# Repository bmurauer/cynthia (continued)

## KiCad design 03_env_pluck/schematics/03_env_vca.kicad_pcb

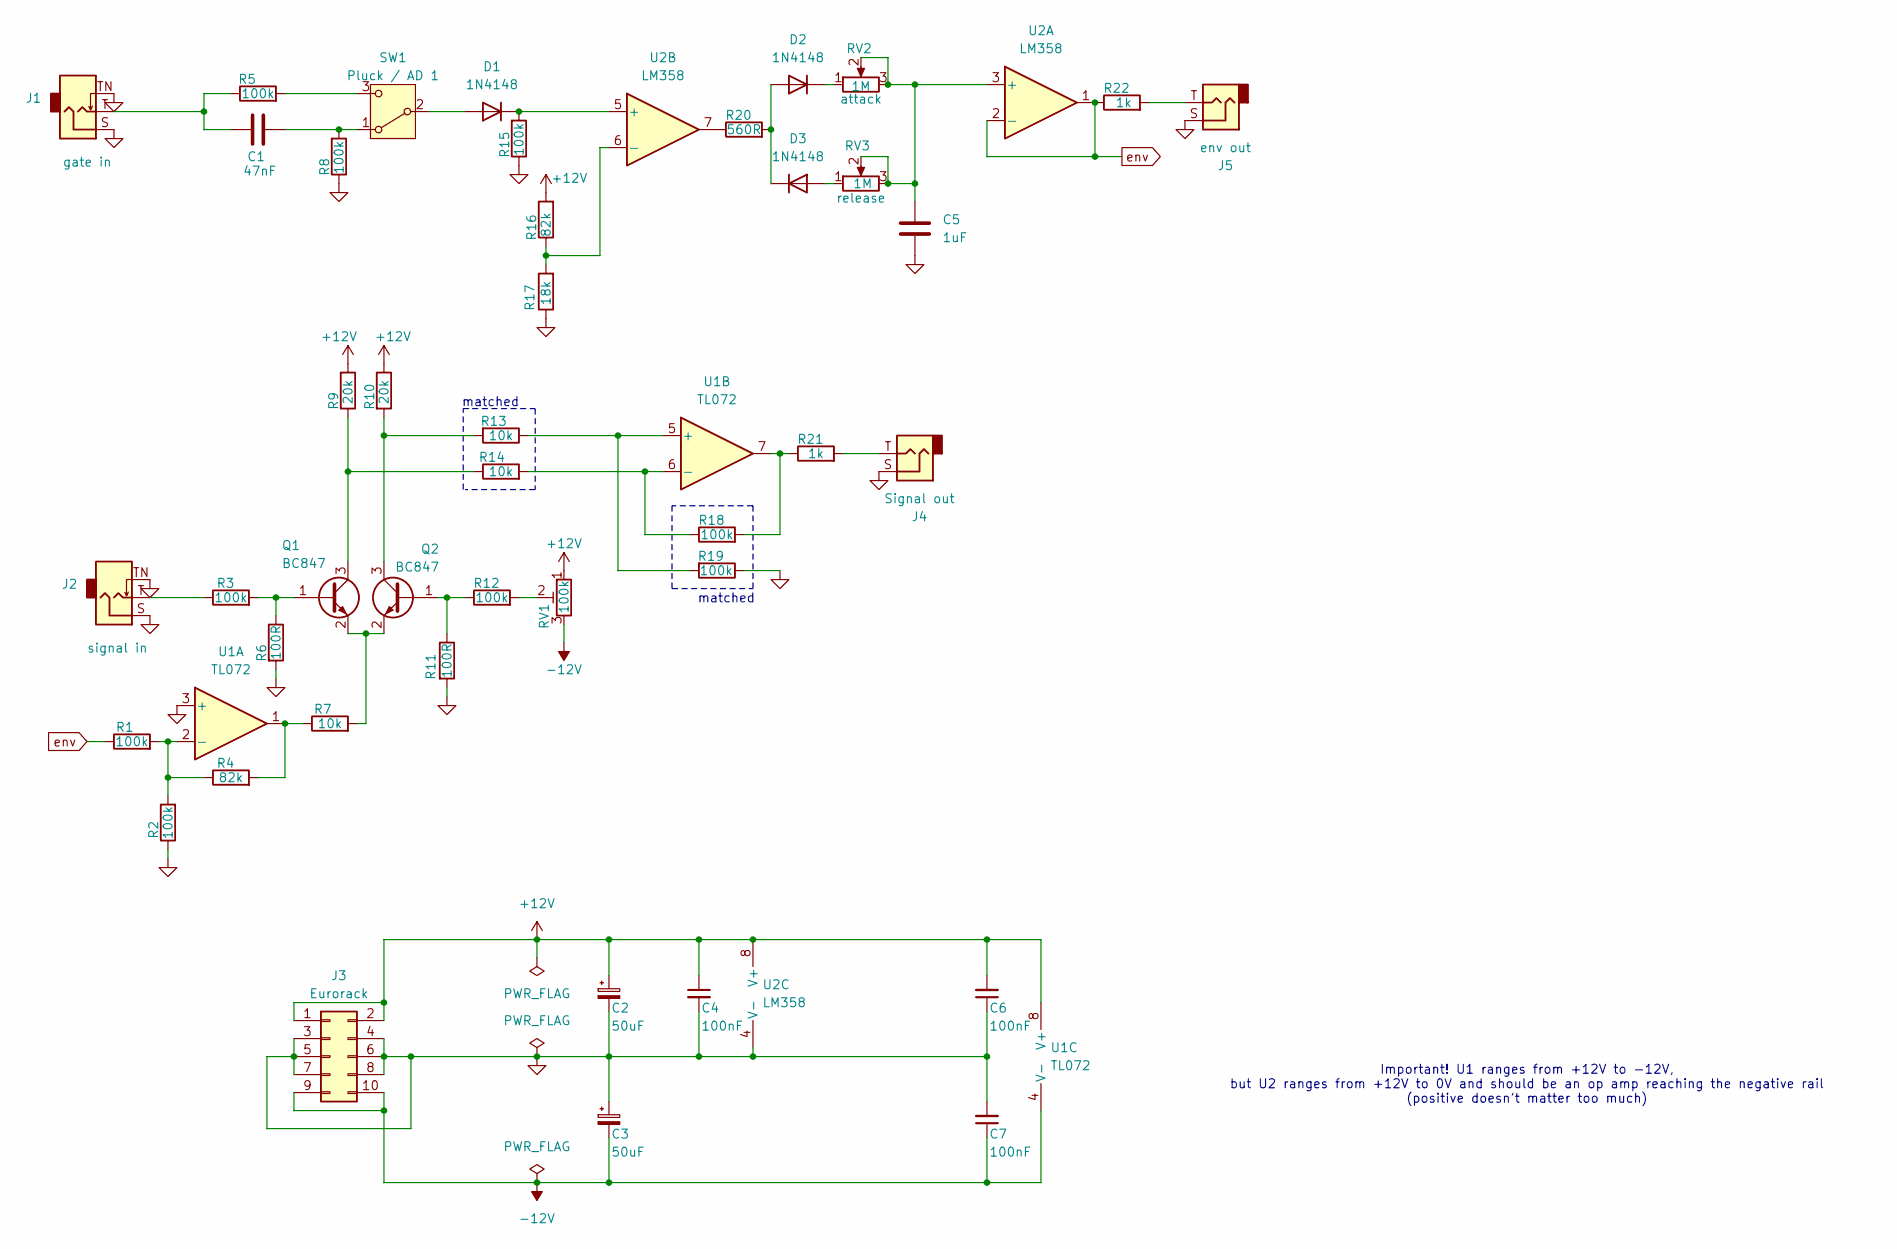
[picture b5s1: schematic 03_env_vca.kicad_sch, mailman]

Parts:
C1: 47nF; C_0805_2012Metric_Pad1.18x1.45mm_HandSolder
C2, C3: 50uF; CP_Radial_D6.3mm_P2.50mm
C4, C6, C7: 100nF; C_0805_2012Metric_Pad1.18x1.45mm_HandSolder
C5: 1uF; C_0805_2012Metric_Pad1.18x1.45mm_HandSolder
D1, D2, D3: 1N4148; D_0805_2012Metric_Pad1.15x1.40mm_HandSolder
J1: gate in; 3.5mm jack mono switched
J2: signal in; 3.5mm jack mono switched
J3: Eurorack; PinHeader_2x05_P2.54mm_Vertical
J4: Signal out; 3.5mm jack mono
J5: env out; 3.5mm jack mono
Q1, Q2: BC847; SOT-23
R1, R2, R3, R5, R8, R12, R15, R18, R19: 100k; R_0805_2012Metric_Pad1.20x1.40mm_HandSolder
R4, R16: 82k; R_0805_2012Metric_Pad1.20x1.40mm_HandSolder
R6, R11: 100R; R_0805_2012Metric_Pad1.20x1.40mm_HandSolder
R7, R13, R14: 10k; R_0805_2012Metric_Pad1.20x1.40mm_HandSolder
R9, R10: 20k; R_0805_2012Metric_Pad1.20x1.40mm_HandSolder
R17: 18k; R_0805_2012Metric_Pad1.20x1.40mm_HandSolder
R20: 560R; R_0805_2012Metric_Pad1.20x1.40mm_HandSolder
R21, R22: 1k; R_0805_2012Metric_Pad1.20x1.40mm_HandSolder
RV1: 100k; trimmer
RV2, RV3: 1M; potientiometer
SW1: Pluck / AD 1; switch
U1: TL072; SOIC-8_3.9x4.9mm_P1.27mm
U2: LM358; SOIC-8_3.9x4.9mm_P1.27mm

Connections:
+12V: C2.1, C4.1, C6.2, J3.1, J3.2, R9.2, R10.1, R16.2, RV1.1, U1.8 (V+), U2.8 (V+)
-12V: C3.2, C7.1, J3.9, J3.10, RV1.3, U1.4 (V-)
GND: C2.2, C3.1, C4.2, C5.2, C6.1, C7.2, J1.S, J1.TN, J2.S, J2.TN, J3.3, J3.4, J3.5, J3.6, J3.7, J3.8, J4.S, J5.S, R2.1, R6.2, R8.1, R11.2, R15.1, R17.1, R19.1, U1.3 (+), U2.4 (V-)
unnamed: C1.1, J1.T, R5.1
unnamed: D1.2 (A), SW1.2 (B)
unnamed: D1.1 (K), R15.2, U2.5 (+)
unnamed: D2.2 (A), D3.1 (K), R20.2
unnamed: D2.1 (K), RV2.1
unnamed: D3.2 (A), RV3.1
unnamed: J2.T, R3.1
unnamed: J4.T, R21.2
unnamed: J5.T, R22.2
unnamed: Q1.1 (B), R3.2, R6.1
unnamed: Q1.3 (C), R9.1, R14.1
unnamed: Q1.2 (E), Q2.2 (E), R7.2
unnamed: Q2.1 (B), R11.1, R12.1
unnamed: Q2.3 (C), R10.2, R13.2
unnamed: R4.2, R7.1, U1.1
unnamed: R12.2, RV1.2
unnamed: R18.2, R21.1, U1.7
unnamed: R20.1, U2.7
unnamed: C1.2, R8.2, SW1.1 (A)
unnamed: R5.2, SW1.3 (C)
unnamed: R1.2, R2.2, R4.1, U1.2 (-)
unnamed: R13.1, R19.2, U1.5 (+)
unnamed: R14.2, R18.1, U1.6 (-)
unnamed: C5.1, RV2.2, RV2.3, RV3.2, RV3.3, U2.3 (+)
unnamed: R16.1, R17.2, U2.6 (-)
env: R1.1, R22.1, U2.1, U2.2 (-)

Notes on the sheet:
matched
Important! U1 ranges from +12V to -12V, but U2 ranges from +12V to 0V and should be an op amp reaching the negative rail (positive doesn't matter too much)

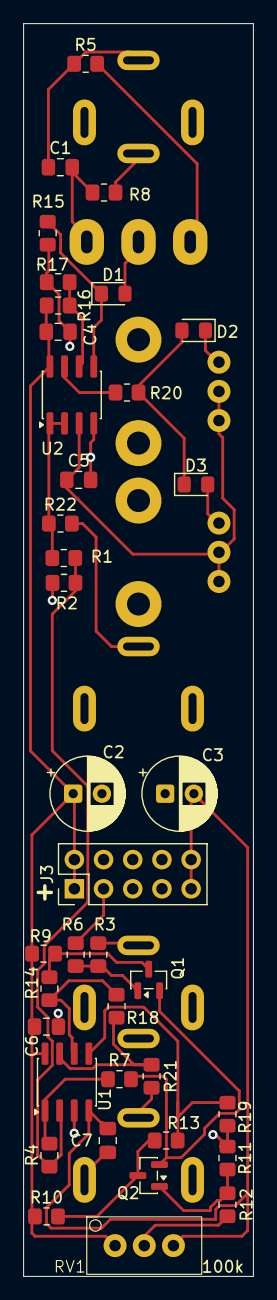
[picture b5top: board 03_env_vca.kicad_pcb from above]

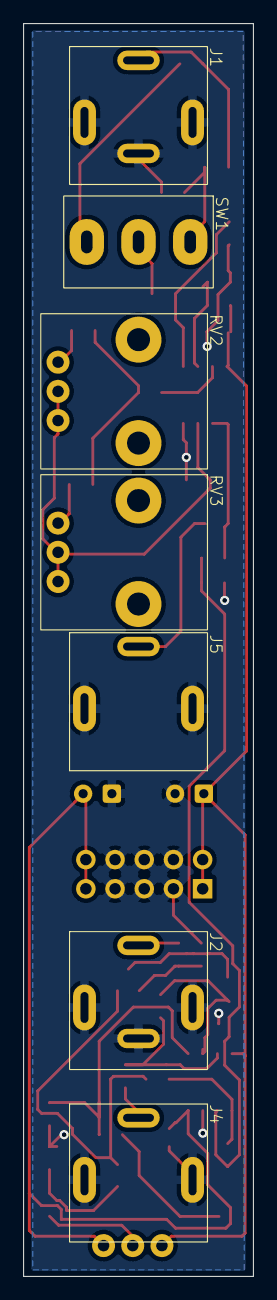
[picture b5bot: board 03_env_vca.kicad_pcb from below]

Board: 2 copper layers, 20.0 x 109.0 mm, 45 parts (7 on the bottom side), 29 nets.

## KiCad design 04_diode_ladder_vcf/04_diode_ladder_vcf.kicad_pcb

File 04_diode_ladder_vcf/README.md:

#04: Diode Ladder VCF

## I/O Specification

Fill in the "Design" columns before building; fill in the "As-Built" columns after assembly and bench testing.

No `.net` file exists for this module yet, so the input/output rows below aren't populated from the schematic. Generate the netlist in KiCad (File > Fabrication Outputs > Netlist, or the equivalent export) and I can fill in the `Ref` / `Label` columns from it — or list the jacks here yourself.

### Inputs

| Ref | Label | Signal Type (Design) | Expected Behavior / Range (Design) | Measured Behavior / Range (As-Built) | Notes |
|-----|-------|-----------------------|--------------------------------------|-----------------------------------------|-------|
| | | | | | |

### Outputs

| Ref | Label | Signal Type (Design) | Expected Behavior / Range (Design) | Measured Behavior / Range (As-Built) | Notes |
|-----|-------|-----------------------|--------------------------------------|-----------------------------------------|-------|
| | | | | | |

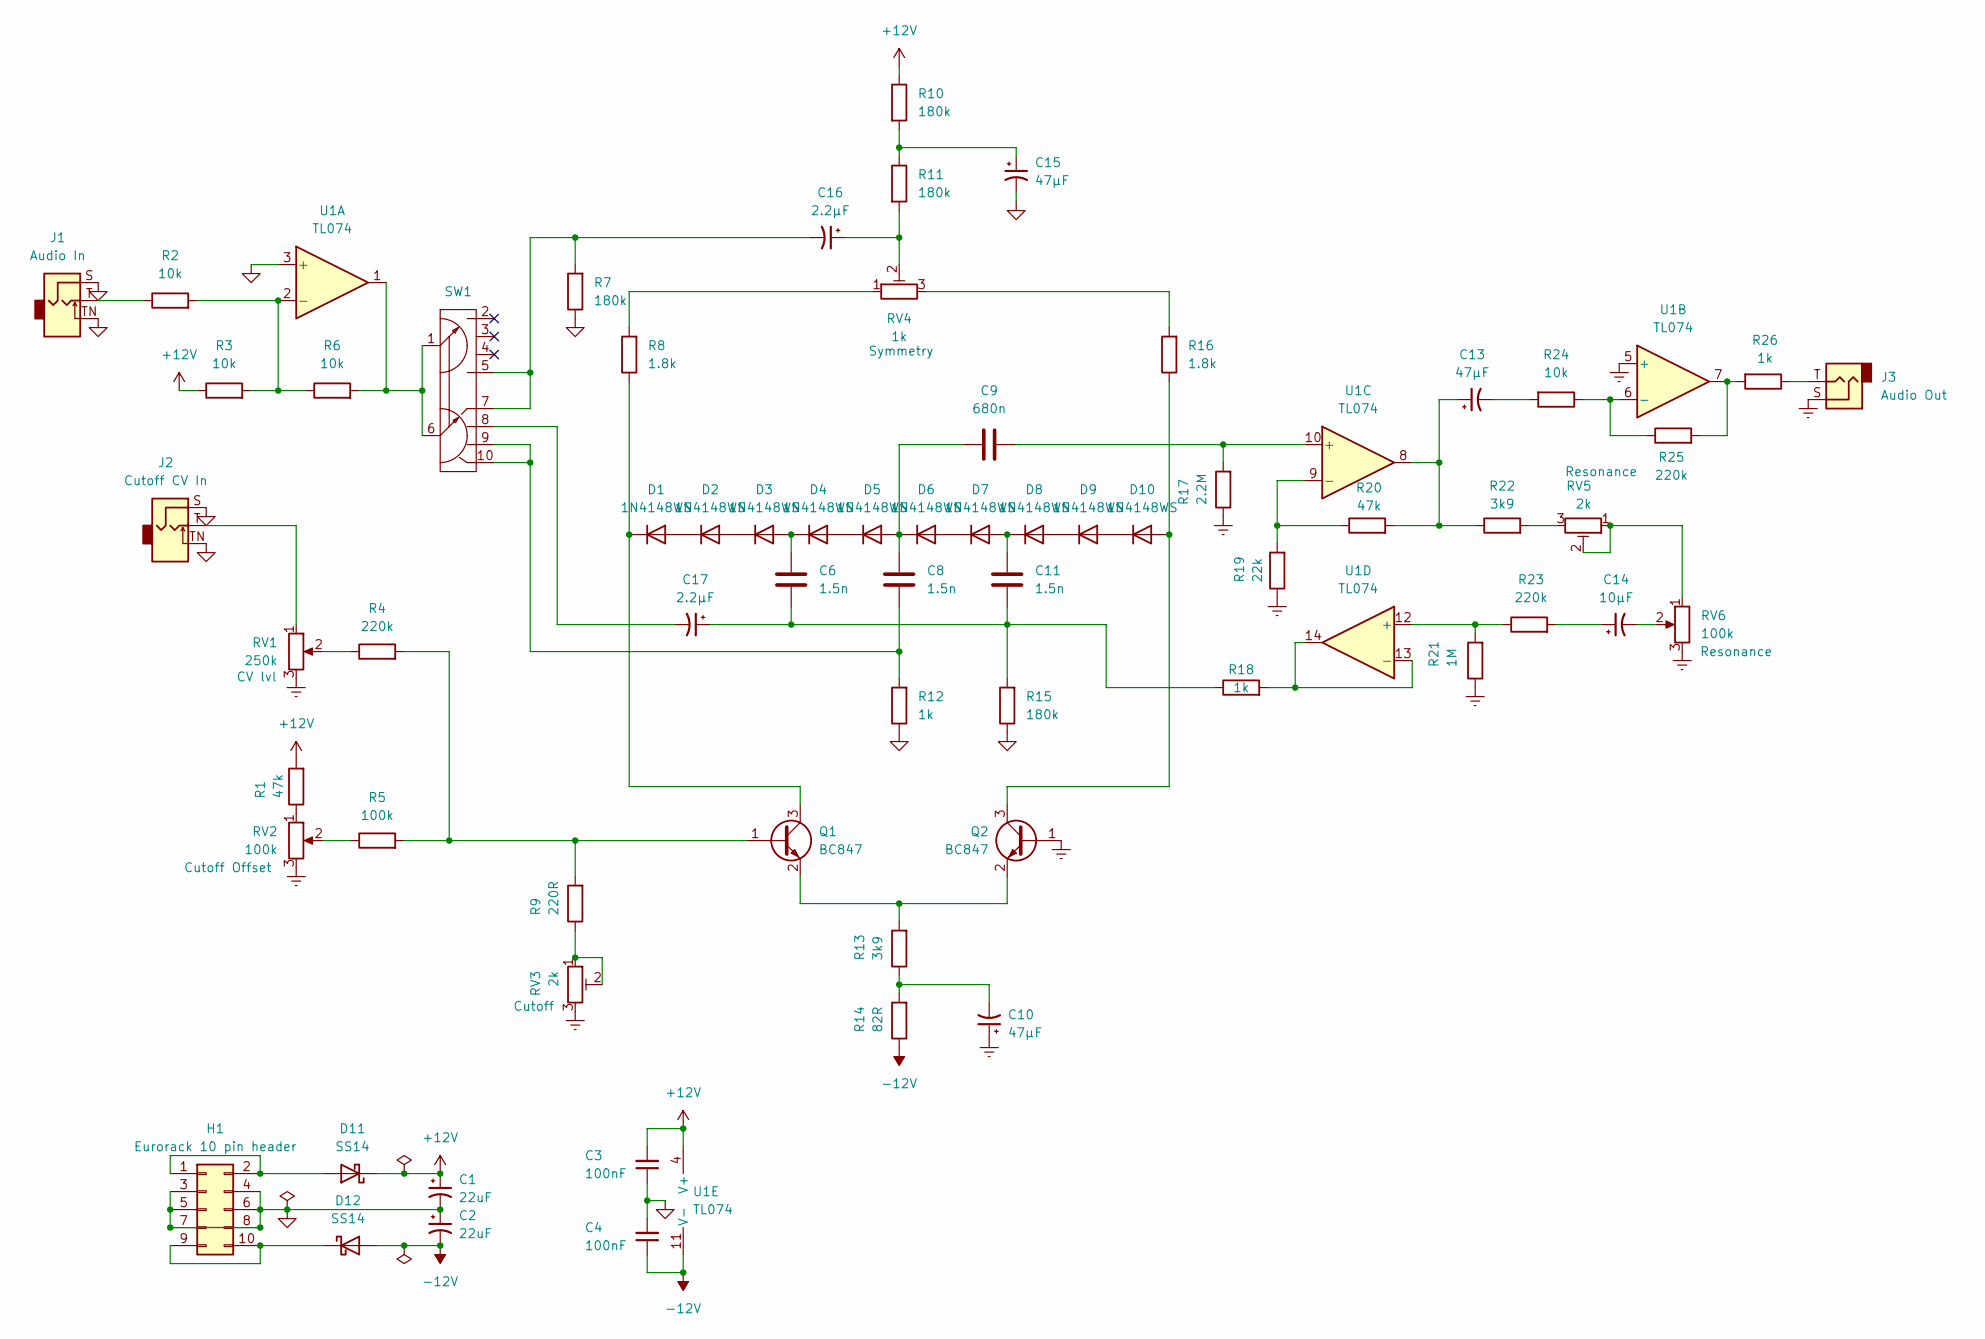
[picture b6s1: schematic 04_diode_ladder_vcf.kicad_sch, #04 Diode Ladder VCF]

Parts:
C1, C2: 22uF; CP_Radial_D6.3mm_P2.50mm
C3, C4: 100nF; C SMD 0805
C6, C8, C11: 1.5n; C SMD 0805
C9: 680n; C_Rect_L10.0mm_W4.0mm_P7.50mm_MKS4
C10, C13, C15: 47μF; CP_Radial_D6.3mm_P2.50mm
C14: 10μF; CP_Radial_D6.3mm_P2.50mm
C16, C17: 2.2μF; CP_Radial_D6.3mm_P2.50mm
D1, D2, D3, D4, D5, D6, D7, D8, D9, D10: 1N4148WS; D_SOD-323_HandSoldering
D11, D12: SS14; D_SMA
H1: Eurorack 10 pin header; Eurorack Header
J1: Audio In; 3.5mm jack mono switched
J2: Cutoff CV In; 3.5mm jack mono switched
J3: Audio Out; 3.5mm jack mono switched
Q1, Q2: BC847; SOT-23
R1, R20: 47k; R SMD 0805
R2, R3, R6, R24: 10k; R SMD 0805
R4, R23, R25: 220k; R SMD 0805
R5: 100k; R SMD 0805
R7, R10, R11, R15: 180k; R SMD 0805
R8, R16: 1.8k; R SMD 0805
R9: 220R; R SMD 0805
R12, R18, R26: 1k; R SMD 0805
R13, R22: 3k9; R SMD 0805
R14: 82R; R SMD 0805
R17: 2.2M; R SMD 0805
R19: 22k; R SMD 0805
R21: 1M; R SMD 0805
RV1: 250k; potientiometer
RV2, RV6: 100k; potientiometer
RV3, RV5: 2k; trimmer
RV4: 1k; trimmer
SW1: switch_linear_2x4
U1: TL074; SOIC-14_3.9x8.7mm_P1.27mm

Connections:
+12V: C1.1, C3.2, D11.1 (K), R1.2, R3.1, R10.1, U1.4 (V+)
-12V: C2.2, C4.1, D12.2 (A), R14.1, U1.11 (V-)
GND: C1.2, C2.1, C3.1, C4.2, H1.3, H1.4, H1.5, H1.6, H1.7, H1.8, J1.S, J1.TN, J2.S, J2.TN, R7.1, R12.1, R15.1, U1.3 (+); also elsewhere on the board
GNDREF: C10.1, J3.S, Q2.1 (B), R17.1, R19.1, R21.1, RV1.3, RV2.3, RV3.3, RV6.3, U1.5 (+)
unnamed 4: C17.2, SW1.8; also elsewhere on the board
unnamed: C8.2, R12.2, SW1.9, SW1.10
unnamed: C10.2, R13.1, R14.2
unnamed 7: C6.2, C11.2, C17.1, R15.2, R18.1; also elsewhere on the board
unnamed 8: C15.1, R10.2, R11.1; also elsewhere on the board
unnamed: C13.1, R20.2, R22.1, U1.8
unnamed: C13.2, R24.2
unnamed: C14.1, R23.2
unnamed: C14.2, RV6.2
unnamed: D1.2 (A), D2.1 (K)
unnamed: D1.1 (K), Q1.3 (C), R8.1
unnamed: D2.2 (A), D3.1 (K)
unnamed: C6.1, D3.2 (A), D4.1 (K)
unnamed: D4.2 (A), D5.1 (K)
unnamed: C8.1, C9.1, D5.2 (A), D6.1 (K)
unnamed: D6.2 (A), D7.1 (K)
unnamed: C11.1, D7.2 (A), D8.1 (K)
unnamed: D8.2 (A), D9.1 (K)
unnamed: D10.2 (A), Q2.3 (C), R16.1
unnamed: D9.2 (A), D10.1 (K)
unnamed: D11.2 (A), H1.1, H1.2
unnamed: D12.1 (K), H1.9, H1.10
unnamed: J1.T, R2.1
unnamed: J2.T, RV1.1
unnamed: J3.T, R26.1
unnamed: Q1.1 (B), R4.2, R5.2, R9.2
unnamed: Q1.2 (E), Q2.2 (E), R13.2
unnamed: R1.1, RV2.1
unnamed: R4.1, RV1.2
unnamed: R5.1, RV2.2
unnamed: R6.2, SW1.1, SW1.6, U1.1
unnamed: R8.2, RV4.1
unnamed: R9.1, RV3.1, RV3.2
unnamed: R16.2, RV4.3
unnamed: R22.2, RV5.3
unnamed: R25.2, R26.2, U1.7
unnamed: RV5.1, RV5.2, RV6.1
unnamed: R2.2, R3.2, R6.1, U1.2 (-)
unnamed: R24.1, R25.1, U1.6 (-)
unnamed: C9.2, R17.2, U1.10 (+)
unnamed: R19.2, R20.1, U1.9 (-)
unnamed: R21.2, R23.1, U1.12 (+)
unnamed: R18.2, U1.13 (-), U1.14

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
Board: 2 copper layers, 66 parts (20 on the bottom side), 49 nets, no tracks yet.

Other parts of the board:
C5, C7: 2.2u; CP_Radial_D6.3mm_P2.50mm
C12: 47u; CP_Radial_D6.3mm_P2.50mm

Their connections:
GND: C12.2; also elsewhere on the board
unnamed 4: C5.2; also elsewhere on the board
unnamed 7: C5.1; also elsewhere on the board
unnamed 8: C12.1; also elsewhere on the board
